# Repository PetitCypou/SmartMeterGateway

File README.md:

SMG - Smart Meter Gateway

This system sends TIC data from an electricity meter over to a TCP Server.
It is currently only designed on L16C6 Landis Gyr meters but could be adapted to Linky ones as well.

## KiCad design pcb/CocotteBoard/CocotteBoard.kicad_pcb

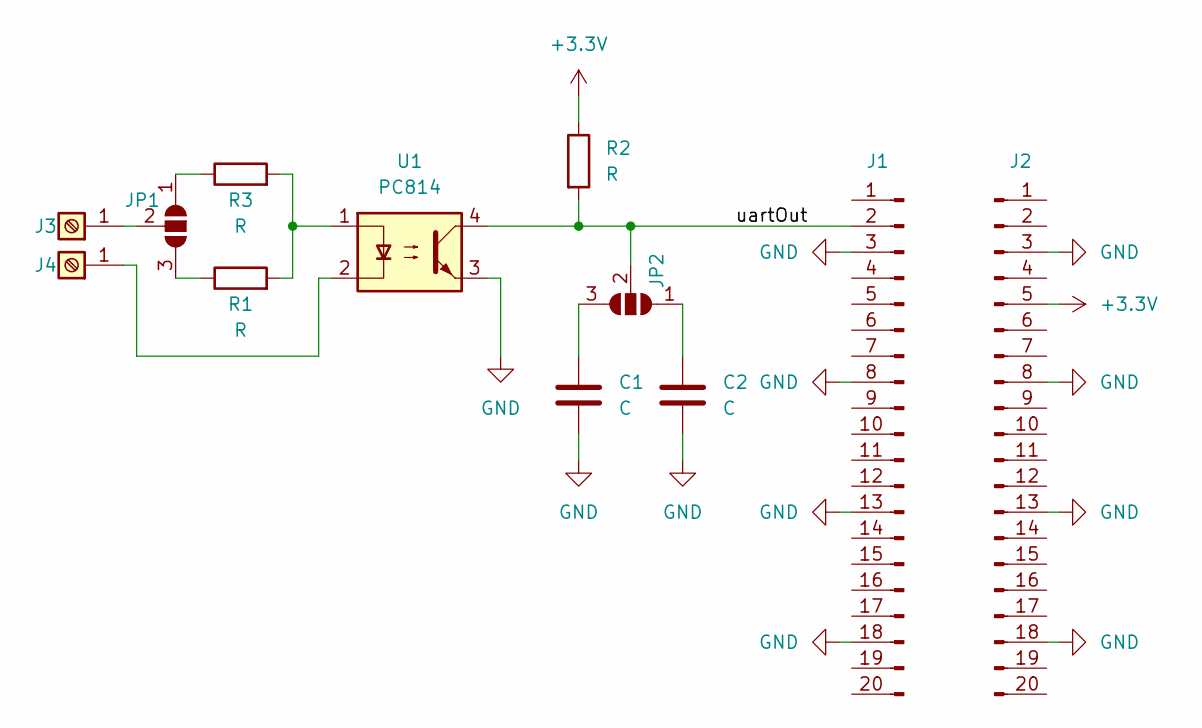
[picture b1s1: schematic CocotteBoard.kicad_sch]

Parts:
C1, C2: C; C_Disc_D3.0mm_W2.0mm_P2.50mm
J1, J2: Conn_01x20_Pin; PinHeader_1x20_P2.54mm_Vertical
J3, J4: Screw_Terminal_01x01; CONN_2065-100&slash_998-403_1_WAG
JP1, JP2: SolderJumper_3_Open; SolderJumper-3_P2.0mm_Open_TrianglePad1.0x1.5mm
R1, R2, R3: R; R_Axial_DIN0207_L6.3mm_D2.5mm_P7.62mm_Horizontal
U1: PC814; DIP-4_W7.62mm

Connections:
+3.3V: J2.5, R2.1
/uart: J1.2, JP2.2 (C), R2.2, U1.4
GND: C1.2, C2.2, J1.3, J1.8, J1.13, J1.18, J2.3, J2.8, J2.13, J2.18, U1.3
unnamed: J3.1, JP1.2 (C)
unnamed: J4.1, U1.2
unnamed: JP1.1 (A), R3.1
unnamed: JP1.3 (B), R1.1
unnamed: C2.1, JP2.1 (A)
unnamed: C1.1, JP2.3 (B)
unnamed: R1.2, R3.2, U1.1

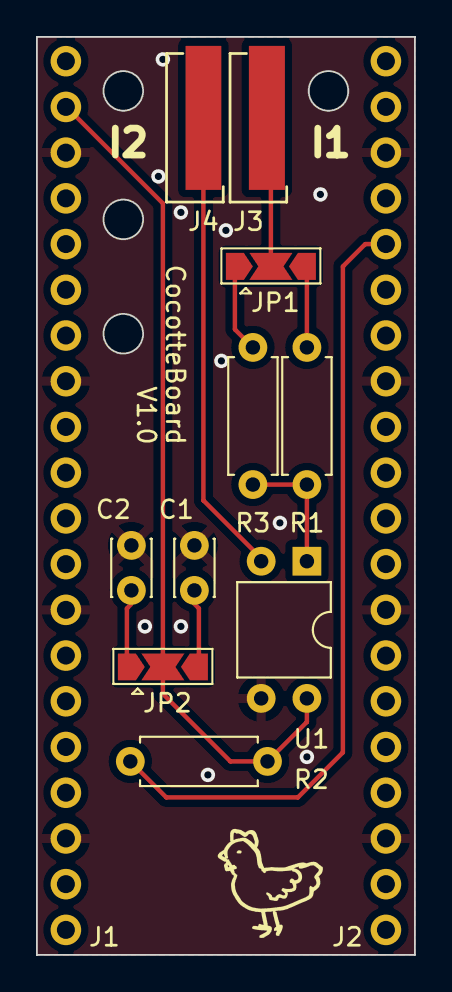
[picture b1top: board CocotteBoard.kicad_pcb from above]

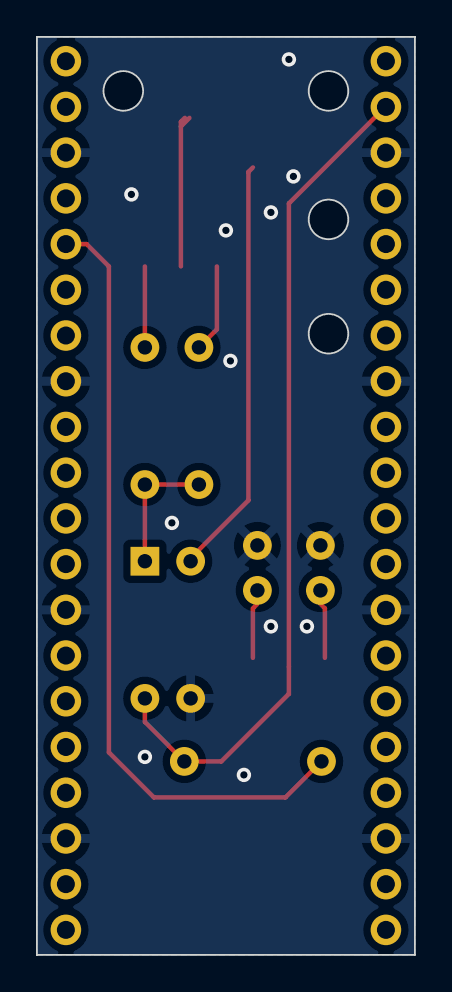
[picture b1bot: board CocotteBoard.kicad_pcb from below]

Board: 2 copper layers, 21.0 x 51.0 mm, 12 parts (2 on the bottom side), 10 nets.

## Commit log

2023-12-19 build: Gitignore & Submodules
2023-12-19 feat: Basic working program
    Implement serial TIC frame parsing, DMA UART acquisition & Ethernet network connectivity into a functional build.
2023-12-19 doc: Graph (dot), references, tools & test circuit example
2023-12-19 feat: FreeRTOS
2023-12-19 feat: WebServer
2023-12-19 feat: DHCP
2023-12-19 feat: FOTA
2023-12-19 feat: IO Manager
2023-12-19 feat: HW schematics v1.0
